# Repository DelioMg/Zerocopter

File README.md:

#  Sistema de Controle de Voo com Raspberry Pi Zero 2W

## Visão Geral

Este projeto tem como objetivo o desenvolvimento de um sistema de controle de voo usando o **Raspberry Pi Zero 2W** e diversos sensores e controladores acoplados para fornecer estabilidade e navegação autônoma a drones.

## Versão 1 (V1)

Na versão inicial do projeto, a configuração inclui:
- **Placa Base** acoplada ao **Raspberry Pi Zero 2W**
- **Câmera** conectada à entrada **MIPI-CSI**
- Sensores integrados:
  - **IMU MPU9250** (sensor de movimento)
  - **Sensor de pressão MS5611**
  - **Conversor ADC ADS1115** para leitura de sinais analógicos
- **Controlador de motores**:
  - A placa possui saídas para conexão direta aos ESCs dos motores
  - A alimentação dos motores é feita por uma bateria **2S**
  - Um **regulador stepdown** de 5V é utilizado para alimentar o Raspberry Pi

Toda a lógica de controle do voo, incluindo a estabilização e processamento dos dados dos sensores, é realizada pelo **Raspberry Pi Zero 2W**.

## Versão 2 (V2)

Na segunda versão do projeto, foram realizadas melhorias significativas para otimizar a estabilidade e o desempenho do sistema:
- Foi adicionado um **microcontrolador RP2040** para gerenciar o controle dos motores e garantir maior precisão na estabilidade do voo
- Um módulo **GPS** foi adicionado ao Raspberry Pi para fornecer dados de localização e permitir a navegação autônoma

## Estrutura do Projeto

- **Hardware**: Raspberry Pi Zero 2W, RP2040, MPU9250, MS5611, ADS1115, regulador stepdown 5V, bateria 2S, câmera, GPS.
- **Software**: Controle de voo implementado no Raspberry Pi Zero 2W (V1), com suporte para integração do RP2040 no controle dos motores (V2).

## Instruções de Uso

1. Clone este repositório:
    ```bash
    git clone https://github.com/DelioMg/Zerocopter.git
    ```
2. Monte a placa base e conecte os componentes de acordo com o diagrama de hardware.
3. Instale as dependências necessárias para o Raspberry Pi Zero 2W e os sensores conectados.
4. Execute o código no Raspberry Pi para iniciar o sistema de controle de voo.

## Melhorias Futuras

- Integração com mais sensores de navegação
- Otimização do tempo de resposta do RP2040 no controle dos motores

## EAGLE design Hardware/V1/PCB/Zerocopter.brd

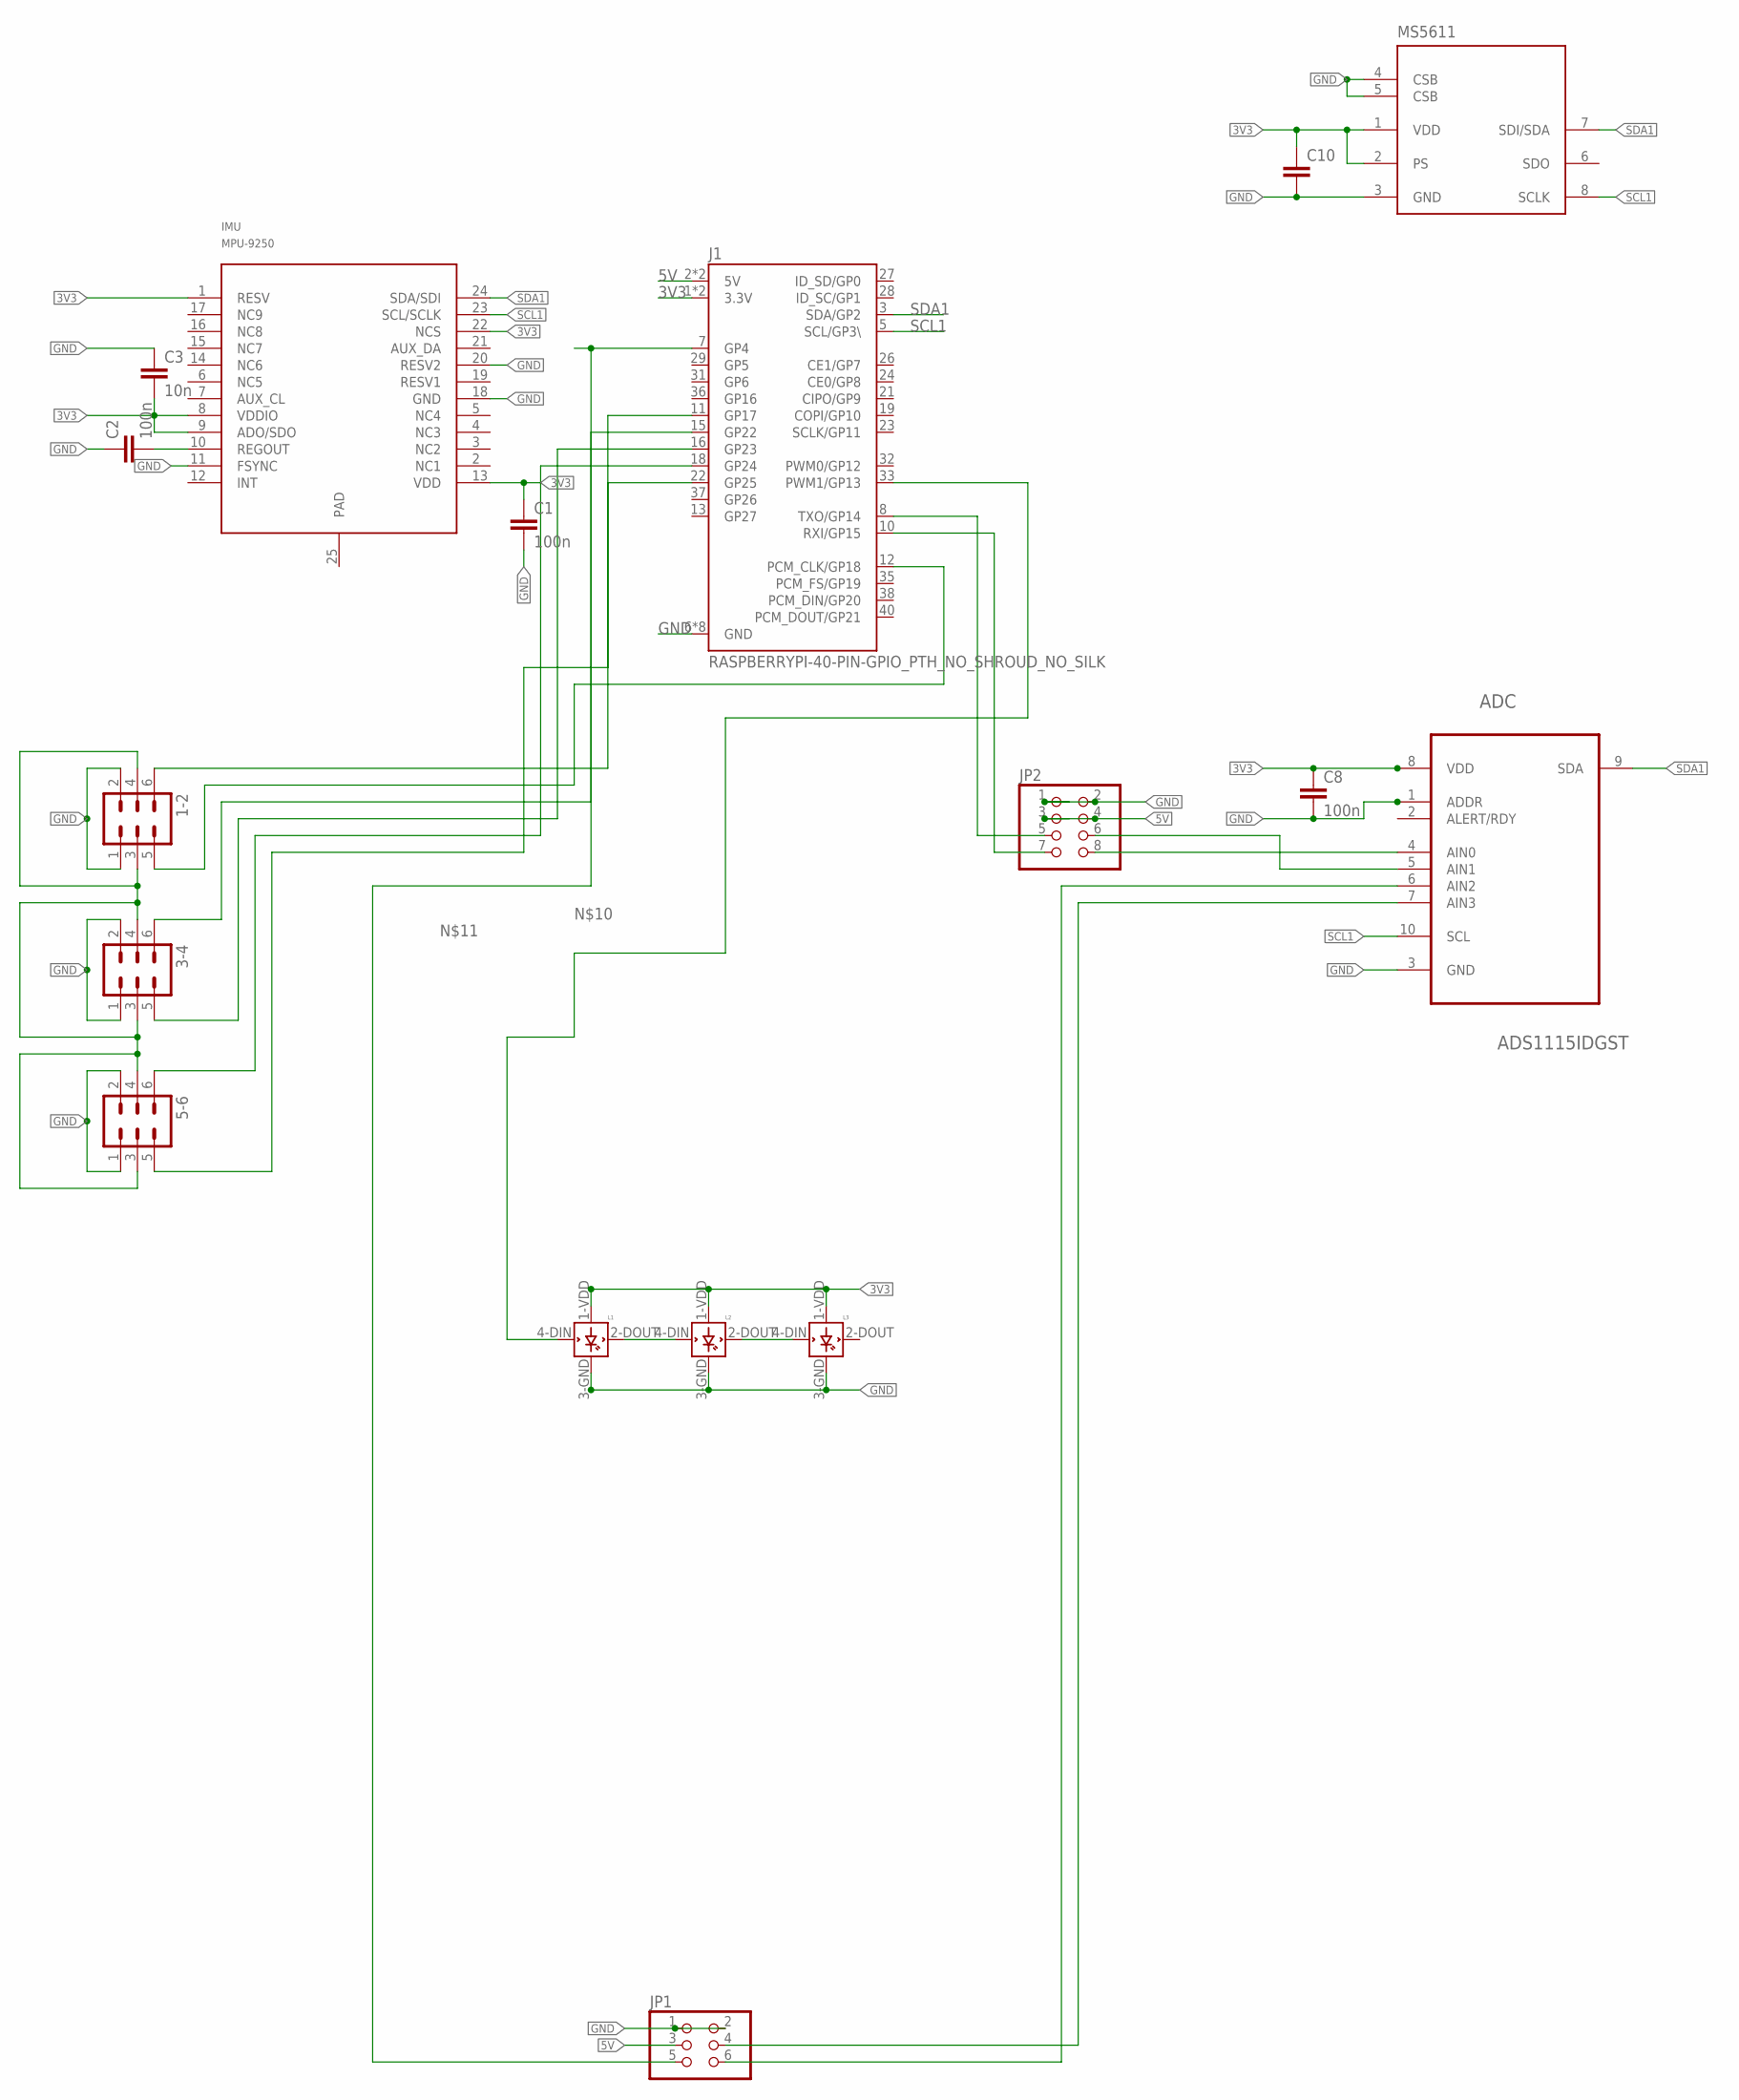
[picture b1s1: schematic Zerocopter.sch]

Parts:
1-2, 3-4, 5-6: MA03-2
ADC: ADS1115IDGST; SOP50P490X110-10N
C1, C2, C8: 100n; C0603
C3: 10n; C0603
C10: C-EUC0603; C0603
IMU: MPU-9250; LEAD-QFN24
J1: RASPBERRYPI-40-PIN-GPIO_PTH_NO_SHROUD_NO_SILK; 2X20_NOSILK
JP1: PINHD-2X3; 2X03
JP2: PINHD-2X4; 2X04
L1, L2, L3: WS2812B
MS5611: MS5611-01BA03; SON125P300X500X100-8N

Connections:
3V3: ADC.8 (VDD), C1.1, C3.2, C8.1, C10.1, IMU.1 (RESV), IMU.8 (VDDIO), IMU.9 (ADO/SDO), IMU.13 (VDD), IMU.22 (NCS), J1.1 (3.3V), J1.17 (3.3V), L1.1-VDD (VDD), L2.1-VDD (VDD), L3.1-VDD (VDD), MS5611.1 (VDD), MS5611.2 (PS)
5V: J1.2 (5V), J1.4 (5V), JP1.3, JP2.3, JP2.4
GND: 1-2.1, 1-2.2, 3-4.1, 3-4.2, 5-6.1, 5-6.2, ADC.1 (ADDR), ADC.3 (GND), C1.2, C2.1, C3.1, C8.2, C10.2, IMU.11 (FSYNC), IMU.18 (GND), IMU.20 (RESV2), J1.6 (GND), J1.9 (GND), J1.14 (GND), J1.20 (GND), J1.25 (GND), J1.30 (GND), J1.34 (GND), J1.39 (GND), JP1.1, JP1.2, JP2.1, JP2.2, L1.3-GND (GND), L2.3-GND (GND), L3.3-GND (GND), MS5611.3 (GND), MS5611.4 (CSB), MS5611.5 (CSB)
unnamed: C2.2, IMU.10 (REGOUT)
unnamed: J1.8 (TXO/GP14), JP2.5
unnamed: L1.2-DOUT (DOUT), L2.4-DIN (DIN)
unnamed: L2.2-DOUT (DOUT), L3.4-DIN (DIN)
unnamed: ADC.6 (AIN2), JP1.6
unnamed: ADC.7 (AIN3), JP1.4
unnamed: 1-2.6, J1.11 (GP17)
unnamed: 1-2.5, J1.12 (PCM_CLK/GP18)
unnamed: J1.33 (PWM1/GP13), L1.4-DIN (DIN)
unnamed: J1.7 (GP4), JP1.5
unnamed: ADC.5 (AIN1), JP2.6
unnamed: 3-4.6, J1.15 (GP22)
unnamed: 3-4.5, J1.16 (GP23)
unnamed: 5-6.6, J1.18 (GP24)
unnamed: 5-6.5, J1.22 (GP25)
unnamed: ADC.4 (AIN0), JP2.8
unnamed: J1.10 (RXI/GP15), JP2.7
unnamed: 1-2.3, 1-2.4, 3-4.3, 3-4.4, 5-6.3, 5-6.4
SCL1: ADC.10 (SCL), IMU.23 (SCL/SCLK), J1.5 (SCL/GP3\), MS5611.8 (SCLK)
SDA1: ADC.9 (SDA), IMU.24 (SDA/SDI), J1.3 (SDA/GP2), MS5611.7 (SDI/SDA)

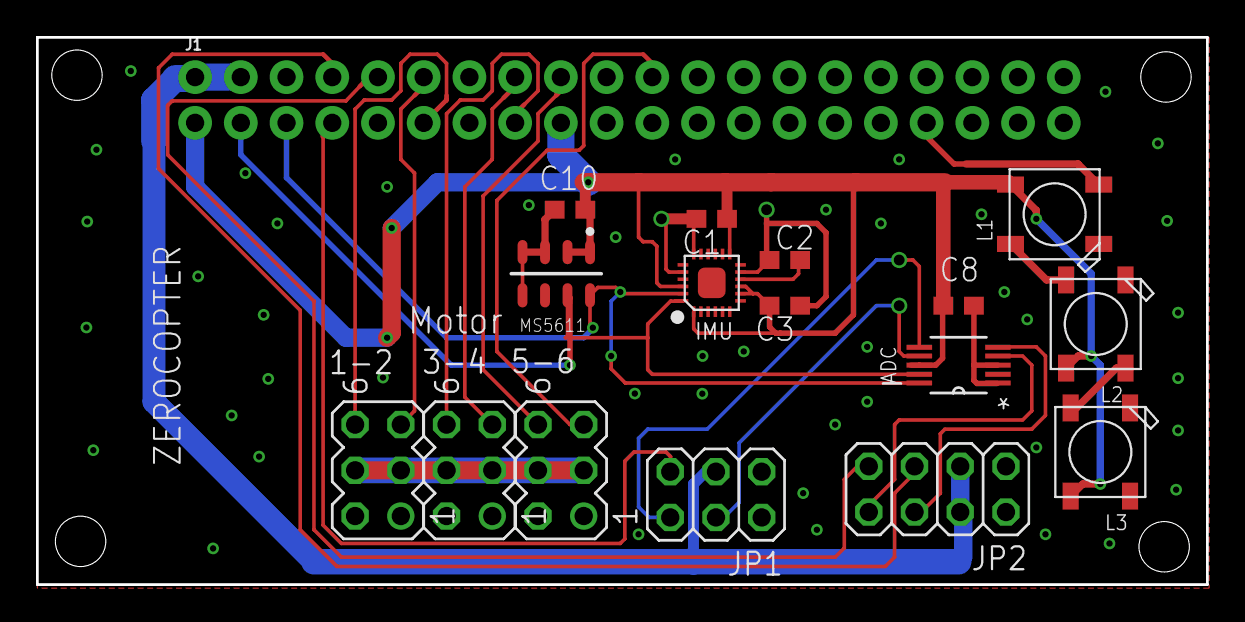
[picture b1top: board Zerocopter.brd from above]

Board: 2 copper layers, 65.0 x 30.4 mm, 17 parts (0 on the bottom side), 23 nets.

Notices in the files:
parts and their libraries:
SparkFun-Connectors: Licensing: Creative Commons ShareAlike 4.0 International - https://creativecommons.org/licenses/by-sa/4.0
